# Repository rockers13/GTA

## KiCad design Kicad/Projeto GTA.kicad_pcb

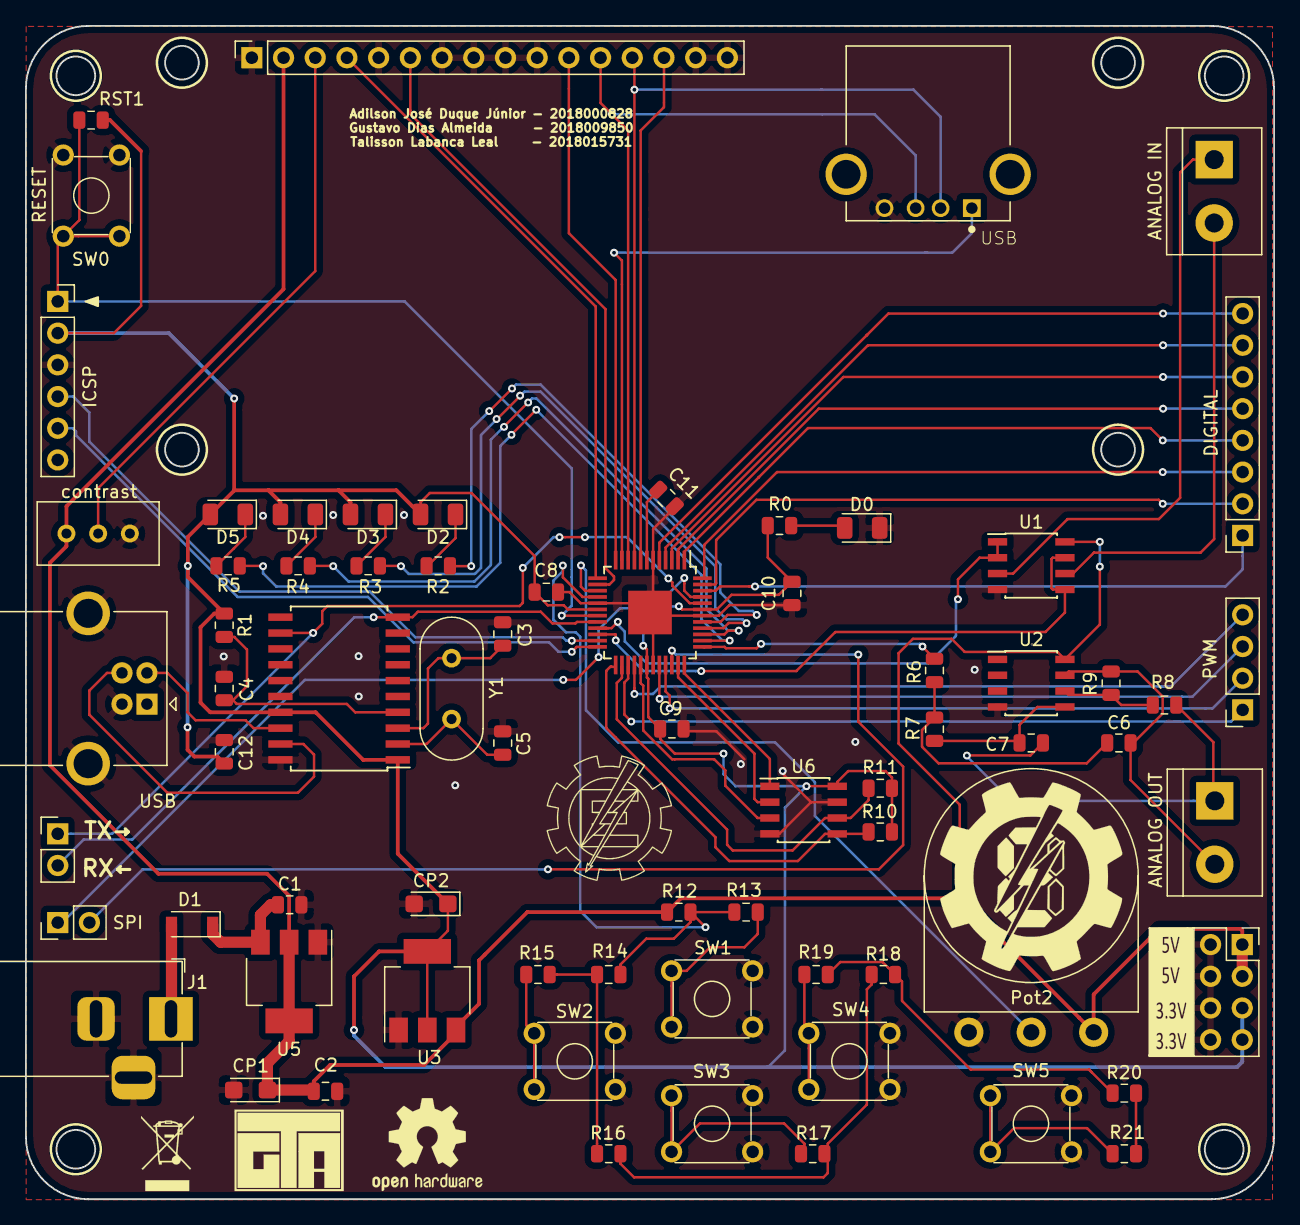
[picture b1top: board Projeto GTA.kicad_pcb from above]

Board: 2 copper layers, 100.0 x 94.0 mm, 71 parts (0 on the bottom side), 73 nets.

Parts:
C1, C2, C3, C4, C5, C6, C7, C8, C9, C10: 100nF; C_0805_2012Metric
C11: 10uF; C_0805_2012Metric
C12: 220nF; C_0805_2012Metric
CP1, CP2: 10uF; CP_EIA-3216-10_Kemet-I
D0, D2, D3, D4, D5: LED; LED_1206_3216Metric
D1: 1N5819; D_SOD-123
IC1: Micro; TQFP-48-1EP_7x7mm_P0.5mm_EP3.5x3.5mm
J1: Barrel Jack 4; BarrelJack_Horizontal
J2: ANALOG IN; TerminalBlock_bornier-2_P5.08mm
J3: ANALOG OUT; TerminalBlock_bornier-2_P5.08mm
J4: PWM; PinSocket_1x04_P2.54mm_Vertical
J5: DIGITAL; PinSocket_1x08_P2.54mm_Vertical
J6: SPI; PinHeader_1x02_P2.54mm_Vertical
J7: TX/RX; PinHeader_1x02_P2.54mm_Vertical
J8: ICSP; PinSocket_1x06_P2.54mm_Vertical
J9: LCD; PinSocket_1x16_P2.54mm_Vertical
J10: Alimentação; PinSocket_2x04_P2.54mm_Vertical
J11: USB; USB_B_OST_USB-B1HSxx_Horizontal
Pot1: 10K; Potentiometer_Bourns_3296W_Vertical
Pot2: 10K; Potentiometer_Omeg_PC16BU_Vertical
R0, R2, R3, R4, R5: 56R; R_0805_2012Metric
R1, R6, R7: 10K; R_0805_2012Metric
R8: 9K1; R_0805_2012Metric
R9: 4K7; R_0805_2012Metric
R10, R11: 10k; R_0805_2012Metric
R12, R13, R14, R15, R16, R17, R18, R19, R20, R21: 1K; R_0805_2012Metric
RST1: 6K8; R_0805_2012Metric
SW0: RESET; SW_TH_Tactile_Omron
SW1, SW2, SW3, SW4, SW5: SW Push; SW_TH_Tactile_Omron
U1, U2: LM358; SOIC-8_3.9x4.9mm_P1.27mm
U3: LD1117S50TR; SOT-223-3_TabPin2
U5: LD1117S33TR; SOT-223-3_TabPin2
U6: 24LC512; SOIC-8_3.9x4.9mm_P1.27mm
USB1: MCP2200-I-SO; SOIC-20W_7.5x12.8mm_P1.27mm
USB2: USB; USB_A
Y1: 12MHz; Crystal_HC49-4H_Vertical

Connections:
3V3: C8.1, C9.2, C10.1, C12.2, CP2.1, D2.2, D3.2, D4.2, D5.2, IC1.18, IC1.30, IC1.43, J8.2, J10.5, J10.7, R0.1, R1.1, R10.1, R11.1, RST1.2, U3.2, U6.8, USB1.1, USB1.17
5V: C2.1, CP1.1, J9.2, J10.1, J10.3, Pot1.1, Pot2.1, R12.1, U1.8, U2.8, U3.3, U5.2
/D+: J11.3, USB1.19
/D-: J11.2, USB1.18
AN9: IC1.15, Pot2.2
B4: IC1.12, J9.11
B5: IC1.10, J9.12, USB2.3
B6: IC1.9, J9.13, USB2.2
B7: IC1.8, J9.14
D1: IC1.41, R2.1
D2: IC1.40, R3.1
D3: IC1.39, R4.1
D4: IC1.38, R5.1
E: IC1.14, J9.6
Filtro: IC1.37, R6.2
GND: C1.2, C2.2, C3.2, C4.2, C5.2, C8.2, C9.1, C10.2, C11.1, C12.1, CP1.2, CP2.2, D0.1, IC1.6, IC1.17, IC1.31, IC1.42, IC1.49, J1.2, J1.3, J8.3, J9.1, J9.5, J9.7, J9.8, J9.9, J9.10, J9.15, J9.16, J10.2, J10.4, J10.6, J10.8, J11.4, J11.5, Pot1.3, Pot2.3, SW0.2, SW0.4, SW1.2, SW1.4, SW2.2, SW2.4, SW3.2, SW3.4, SW4.2, SW4.4, SW5.2, SW5.4, U1.4, U2.4, U3.1, U5.1, U6.4, U6.7, USB1.20, USB2.4
IO1: IC1.1, J5.4
IO2: IC1.2, J5.5
IO3: IC1.3, J5.6
IO4: IC1.4, J5.7
IO5: IC1.5, J5.8
IO29: IC1.29, U6.3
IO35: IC1.35, U6.2
IO36: IC1.36, U6.1
IO46: IC1.46, J5.1
IO47: IC1.47, J5.2
IO48: IC1.48, J5.3
MCLR: IC1.19, J8.1, RST1.1, SW0.1, SW0.3
unnamed: C1.1, D1.1, U5.3
unnamed: C3.1, USB1.3, Y1.2
unnamed: C4.1, R1.2, USB1.4
unnamed: C5.1, USB1.2, Y1.1
unnamed: C6.1, R6.1, R7.2
unnamed: C6.2, J3.2, R9.1, U2.7
unnamed: C7.1, R7.1, U2.5
unnamed: C7.2, J3.1, R8.2
unnamed: D0.2, R0.2
unnamed: D1.2, J1.1
unnamed: D2.1, R2.2
unnamed: D3.1, R3.2
unnamed: D4.1, R4.2
unnamed: D5.1, R5.2
unnamed: J2.1, U1.3
unnamed: J2.2, U1.6
unnamed: J9.3, Pot1.2
unnamed: R8.1, R9.2, U2.6
unnamed: R13.2, SW1.1, SW1.3
unnamed: R14.2, R15.1, R16.1
unnamed: R15.2, SW2.1, SW2.3
unnamed: R16.2, R17.1, R18.1
unnamed: R17.2, SW3.1, SW3.3
unnamed: R18.2, R19.1, R20.1
unnamed: R19.2, SW4.1, SW4.3
unnamed: R20.2, R21.1
unnamed: R21.2, SW5.1, SW5.3
PGEC: IC1.24, J8.5
PGED: IC1.23, J8.4
PWM27: IC1.27, J4.1
PWM28: IC1.28, J4.4
PWM32: IC1.32, J4.3
PWM33: IC1.33, J4.2
RA0: IC1.21, U1.1, U1.2
RA1: IC1.22, U1.5, U1.7
RS: IC1.13, J9.4
RX: IC1.20, J7.2, USB1.10
SCL: IC1.26, R11.2, U6.6
SDA: IC1.25, R10.2, U6.5
SPI34: IC1.34, J6.2
SPI45: IC1.45, J6.1
SW: IC1.16, R12.2, R13.1, R14.1
TX: IC1.44, J7.1, USB1.12
VCAP: C11.2, IC1.7
VUSB: IC1.11, USB2.1
